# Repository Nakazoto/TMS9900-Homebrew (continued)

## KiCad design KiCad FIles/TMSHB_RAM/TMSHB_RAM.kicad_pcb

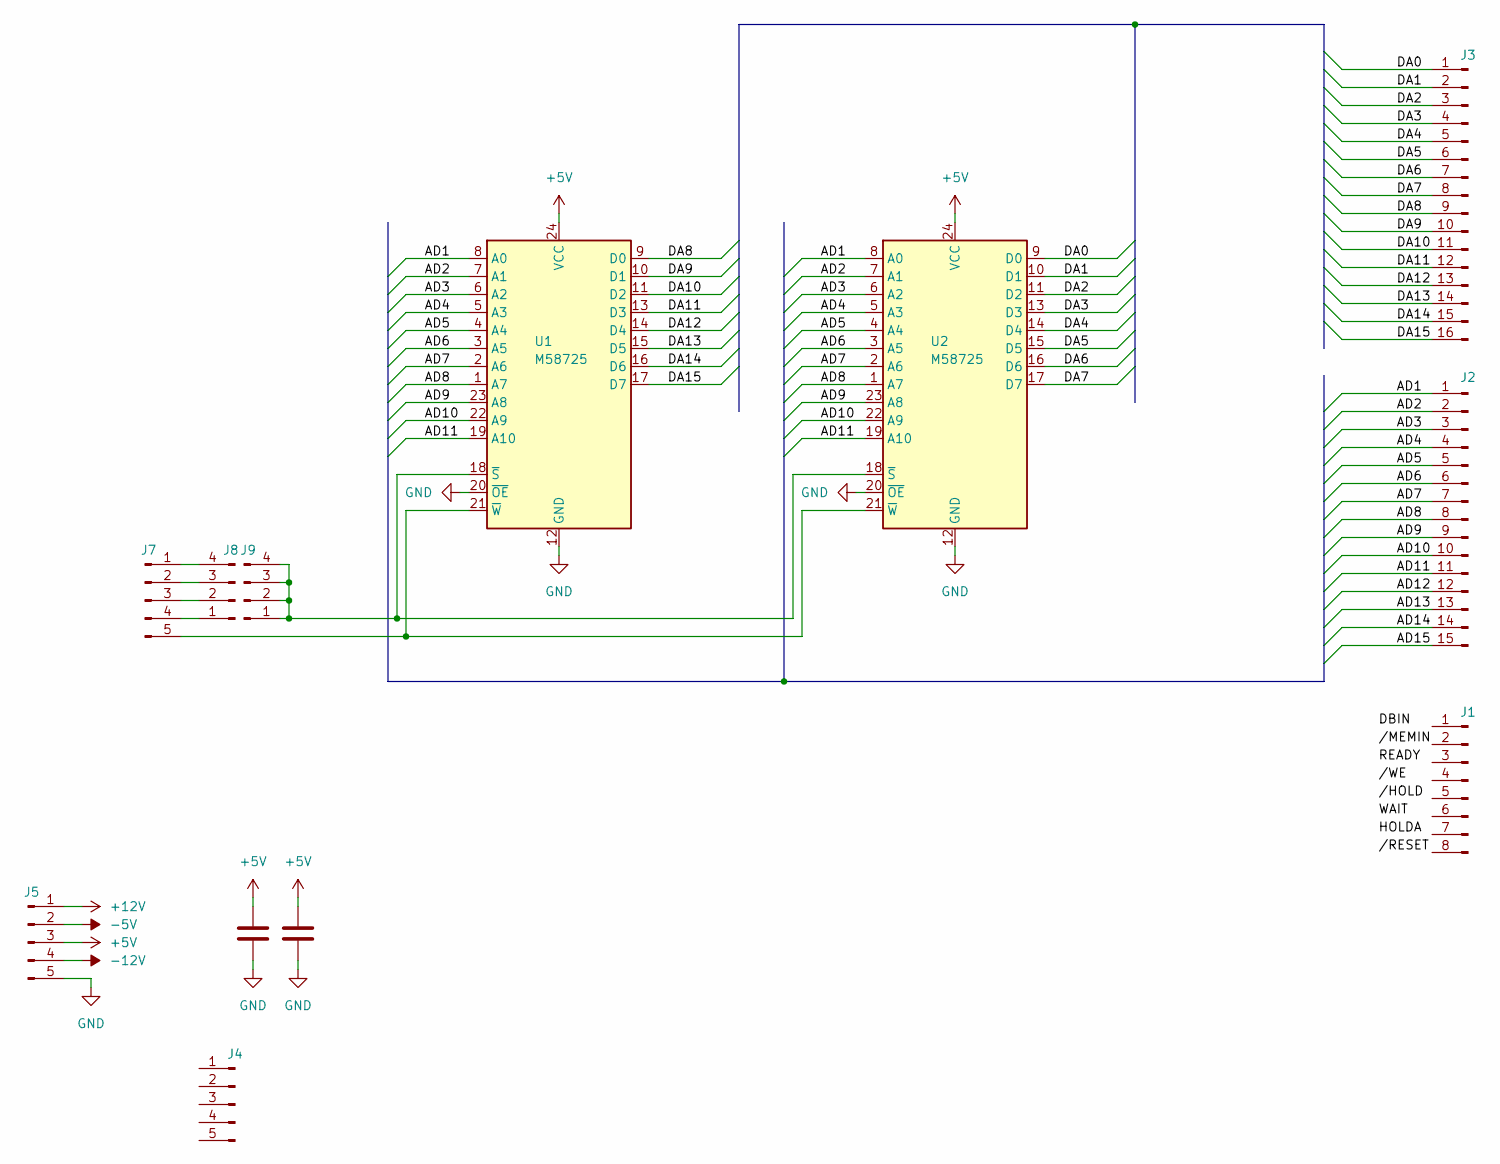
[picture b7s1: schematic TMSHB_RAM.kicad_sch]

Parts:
C1, C2: C; C_Disc_D3.0mm_W1.6mm_P2.50mm
J1: Conn_01x08_Pin; PinHeader_1x08_P2.54mm_Vertical
J2: Conn_01x15_Pin; PinHeader_1x15_P2.54mm_Vertical
J3: Conn_01x16_Pin; PinHeader_1x16_P2.54mm_Vertical
J4, J5, J7: Conn_01x05_Pin; PinHeader_1x05_P2.54mm_Vertical
J8, J9: Conn_01x04_Pin; PinHeader_1x04_P2.54mm_Vertical
U1, U2: M58725; DIP-24_W15.24mm

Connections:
+5V: C1.1, C2.1, J5.3, U1.24 (VCC), U2.24 (VCC)
+12V: J5.1
-5V: J5.2
-12V: J5.4
/AD1: J2.1, U1.8 (A0), U2.8 (A0)
/AD2: J2.2, U1.7 (A1), U2.7 (A1)
/AD3: J2.3, U1.6 (A2), U2.6 (A2)
/AD4: J2.4, U1.5 (A3), U2.5 (A3)
/AD5: J2.5, U1.4 (A4), U2.4 (A4)
/AD6: J2.6, U1.3 (A5), U2.3 (A5)
/AD7: J2.7, U1.2 (A6), U2.2 (A6)
/AD8: J2.8, U1.1 (A7), U2.1 (A7)
/AD9: J2.9, U1.23 (A8), U2.23 (A8)
/AD10: J2.10, U1.22 (A9), U2.22 (A9)
/AD11: J2.11, U1.19 (A10), U2.19 (A10)
/AD12: J2.12
/AD13: J2.13
/AD14: J2.14
/AD15: J2.15
/DA0: J3.1, U2.9 (D0)
/DA1: J3.2, U2.10 (D1)
/DA2: J3.3, U2.11 (D2)
/DA3: J3.4, U2.13 (D3)
/DA4: J3.5, U2.14 (D4)
/DA5: J3.6, U2.15 (D5)
/DA6: J3.7, U2.16 (D6)
/DA7: J3.8, U2.17 (D7)
/DA8: J3.9, U1.9 (D0)
/DA9: J3.10, U1.10 (D1)
/DA10: J3.11, U1.11 (D2)
/DA11: J3.12, U1.13 (D3)
/DA12: J3.13, U1.14 (D4)
/DA13: J3.14, U1.15 (D5)
/DA14: J3.15, U1.16 (D6)
/DA15: J3.16, U1.17 (D7)
GND: C1.2, C2.2, J5.5, U1.12 (GND), U1.20 (~OE), U2.12 (GND), U2.20 (~OE)
unnamed: J7.1, J8.4
unnamed: J7.2, J8.3
unnamed: J7.3, J8.2
unnamed: J7.4, J8.1
unnamed: J7.5, U1.21 (~W), U2.21 (~W)
unnamed: J9.1, J9.2, J9.3, J9.4, U1.18 (~S), U2.18 (~S)

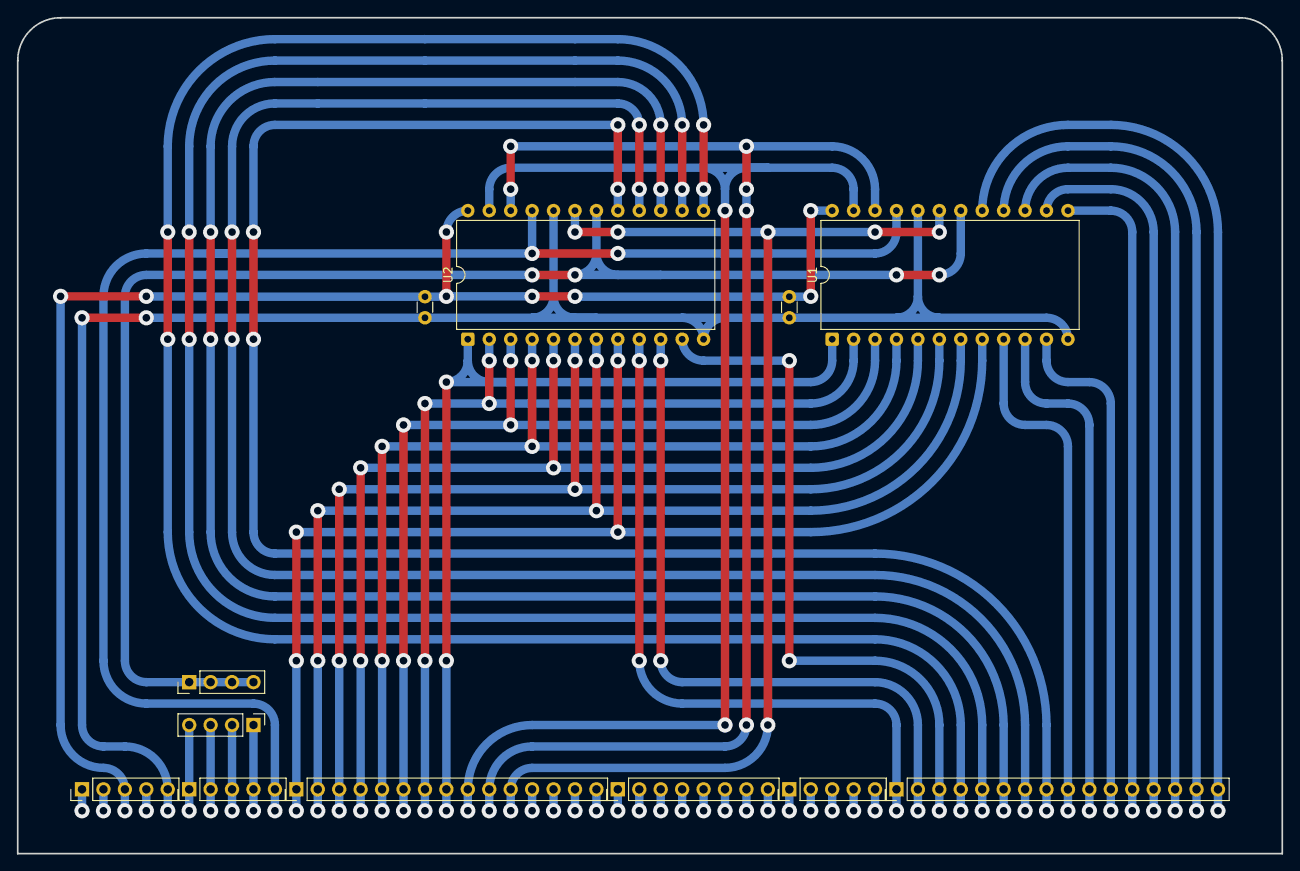
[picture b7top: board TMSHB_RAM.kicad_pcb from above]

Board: 2 copper layers, 149.9 x 99.1 mm, 12 parts (0 on the bottom side), 35 nets.

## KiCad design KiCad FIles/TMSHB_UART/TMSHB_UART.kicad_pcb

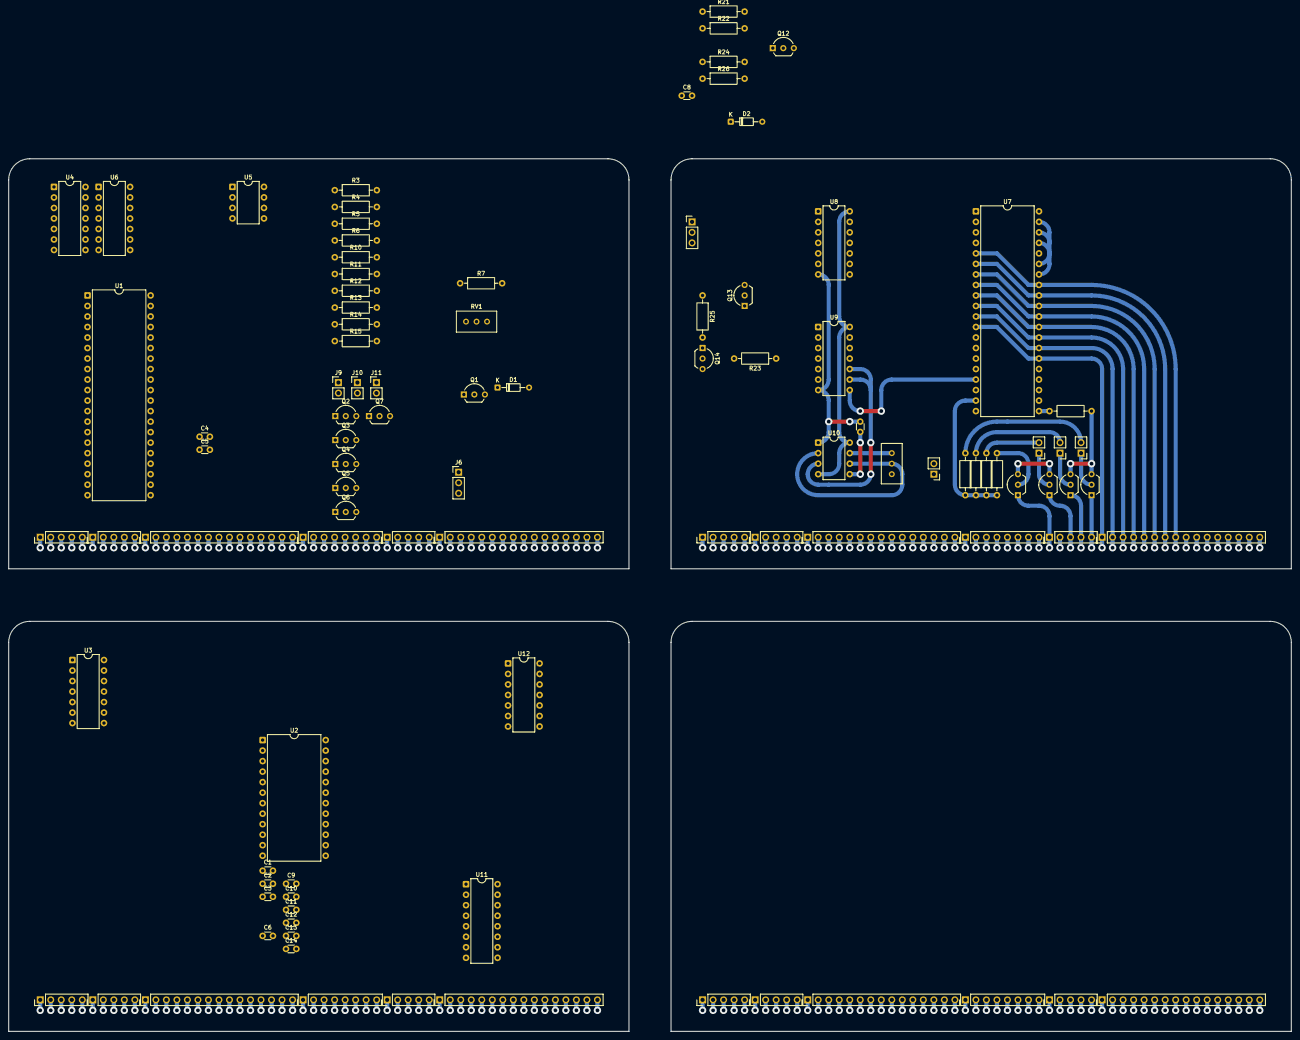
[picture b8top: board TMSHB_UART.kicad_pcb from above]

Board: 2 copper layers, 309.9 x 210.8 mm, 99 parts (0 on the bottom side), 117 nets.

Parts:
C1, C2, C3, C6, C9, C10, C11, C12, C13, C14: C; C_Disc_D3.0mm_W1.6mm_P2.50mm
C4: 470nF; C_Disc_D3.0mm_W1.6mm_P2.50mm
C5, C7: 0.1u; C_Disc_D3.0mm_W1.6mm_P2.50mm
C8: 10nF; C_Disc_D3.0mm_W1.6mm_P2.50mm
D1, D2: D; D_DO-34_SOD68_P7.62mm_Horizontal
J1, J1#2, J1#3, J1#4: Conn_01x08_Pin; PinHeader_1x08_P2.54mm_Vertical
J2, J2#2, J2#3, J2#4: Conn_01x15_Pin; PinHeader_1x15_P2.54mm_Vertical
J3, J3#2, J3#3, J3#4: Conn_01x16_Pin; PinHeader_1x16_P2.54mm_Vertical
J4, J4#2, J4#3, J4#4, J5, J5#2, J5#3, J5#4, J7, J7#2, J7#3, J7#4: Conn_01x05_Pin; PinHeader_1x05_P2.54mm_Vertical
J6, J8: Conn_01x03_Pin; PinHeader_1x03_P2.54mm_Vertical
J9, J10, J11, J12, J13, J14, J14#2: Conn_01x02_Pin; PinHeader_1x02_P2.54mm_Vertical
Q1, Q3, Q4, Q5, Q6, Q7, Q8, Q9, Q10, Q11, Q12, Q13: NPN; TO-92_Inline_Wide
Q2, Q14: PNP; TO-92_Inline_Wide
R3, R11, R16, R22: 4.7k; R_Axial_DIN0207_L6.3mm_D2.5mm_P10.16mm_Horizontal
R4, R26: 1k; R_Axial_DIN0207_L6.3mm_D2.5mm_P10.16mm_Horizontal
R5, R6, R7, R10, R12, R13, R14, R15, R17, R18, R19, R20, R21, R23, R24, R25: 10k; R_Axial_DIN0207_L6.3mm_D2.5mm_P10.16mm_Horizontal
RV1: 5k; Potentiometer_Bourns_3296W_Vertical
RV2: 10k; Potentiometer_Bourns_3296W_Vertical
U1, U7: TR1602; DIP-40_W15.24mm
U2: 27C16; DIP-24_W15.24mm
U3, U6, U8: 74LS00; DIP-14_W7.62mm
U4, U9: 74LS32; DIP-14_W7.62mm
U5, U10: NE555P; DIP-8_W7.62mm
U11: 74LS138; DIP-16_W7.62mm
U12: 74LS04; DIP-14_W7.62mm

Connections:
+5V: C1.1, C2.1, C3.1, C6.1, C9.1, C10.1, C11.1, C12.1, C13.1, C14.1, J5.3, J5#2.3, J5#3.3, J5#4.3, Q2.3 (E), Q14.3 (E), R4.1, R11.1, R22.1, R26.1, U1.1 (+5V), U1.16 (SFD), U1.34 (CRL), U1.35 (PI), U1.37 (WSL2), U1.38 (WSL1), U1.39 (EPE), U2.21 (VPP), U2.24 (VCC), U3.14 (VCC), U4.14 (VCC), U5.4 (R), U5.8 (VCC), U6.14 (VCC), U7.1 (+5V), U7.16 (SFD), U7.34 (CRL), U7.35 (PI), U7.37 (WSL2), U7.38 (WSL1), U7.39 (EPE), U8.14 (VCC), U9.14 (VCC), U10.4 (R), U10.8 (VCC), U11.6 (E3), U11.16 (VCC), U12.14 (VCC)
+12V: J5.1, J5#2.1, J5#3.1, J5#4.1
-5V: J5.2, J5#2.2, J5#3.2, J5#4.2
-12V: J5.4, J5#2.4, J5#3.4, J5#4.4, R7.1, R25.1, U1.2 (-12V), U7.2 (-12V)
/AD1: J2.1, J2#2.1, J2#3.1, J2#4.1, U2.8 (A0)
/AD2: J2.2, J2#2.2, J2#3.2, J2#4.2, U2.7 (A1)
/AD3: J2.3, J2#2.3, J2#3.3, J2#4.3, U2.6 (A2)
/AD4: J2.4, J2#2.4, J2#3.4, J2#4.4, U2.5 (A3)
/AD5: J2.5, J2#2.5, J2#3.5, J2#4.5, U2.4 (A4)
/AD6: J2.6, J2#2.6, J2#3.6, J2#4.6, U2.3 (A5)
/AD7: J2.7, J2#2.7, J2#3.7, J2#4.7, U2.2 (A6)
/AD8: J2.8, J2#2.8, J2#3.8, J2#4.8, U2.1 (A7)
/AD9: J2.9, J2#2.9, J2#3.9, J2#4.9, U2.23 (A8)
/AD10: J2.10, J2#2.10, J2#3.10, J2#4.10, U2.22 (A9)
/AD11: J2.11, J2#2.11, J2#3.11, J2#4.11, U2.19 (A10)
/AD12: J2.12, J2#2.12, J2#3.12, J2#4.12, U3.1
/AD13: J2.13, J2#2.13, J2#3.13, J2#4.13, U3.2
/AD14: J2.14, J2#2.14, J2#3.14, J2#4.14, U3.4
/AD15: J2.15, J2#2.15, J2#3.15, J2#4.15, U3.5
/DA8: J3.9, J3#2.9, J3#3.9, J3#4.9
/DA9: J3.10, J3#2.10, J3#3.10, J3#4.10
/DA10: J3.11, J3#2.11, J3#3.11, J3#4.11
/DA11: J3.12, J3#2.12, J3#3.12, J3#4.12
/DA12: J3.13, J3#2.13, J3#3.13, J3#4.13
/DA13: J3.14, J3#2.14, J3#3.14, J3#4.14
/DA14: J3.15, J3#2.15, J3#3.15, J3#4.15
/DA15: J3.16, J3#2.16, J3#3.16, J3#4.16
/DBIN: J1.1, J1#2.1, J1#3.1, J1#4.1
/HOLDA: J1.7, J1#2.7, J1#3.7, J1#4.7
/READY: J1.3, J1#2.3, J1#3.3, J1#4.3
/WAIT: J1.6, J1#2.6, J1#3.6, J1#4.6
//HOLD: J1.5, J1#2.5, J1#3.5, J1#4.5
//MEMIN: J1.2, J1#2.2, J1#3.2, J1#4.2
//RESET: J1.8, J1#2.8, J1#3.8, J1#4.8
//WE: J1.4, J1#2.4, J1#3.4, J1#4.4
DA0: J3.1, J3#2.1, J3#3.1, J3#4.1, Q1.1 (C), Q12.1 (C), U1.12 (RR1), U1.26 (TR1), U7.12 (RR1), U7.26 (TR1)
DA1: J3.2, J3#2.2, J3#3.2, J3#4.2, U1.11 (RR2), U1.27 (TR2), U7.11 (RR2), U7.27 (TR2)
DA2: J3.3, J3#2.3, J3#3.3, J3#4.3, U1.10 (RR3), U1.28 (TR3), U7.10 (RR3), U7.28 (TR3)
DA3: J3.4, J3#2.4, J3#3.4, J3#4.4, U1.9 (RR4), U1.29 (TR4), U7.9 (RR4), U7.29 (TR4)
DA4: J3.5, J3#2.5, J3#3.5, J3#4.5, U1.8 (RR5), U1.30 (TR5), U7.8 (RR5), U7.30 (TR5)
DA5: J3.6, J3#2.6, J3#3.6, J3#4.6, U1.7 (RR6), U1.31 (TR6), U7.7 (RR6), U7.31 (TR6)
DA6: J3.7, J3#2.7, J3#3.7, J3#4.7, U1.6 (RR7), U1.32 (TR7), U7.6 (RR7), U7.32 (TR7)
DA7: J3.8, J3#2.8, J3#3.8, J3#4.8, U1.5 (RR8), U1.33 (TR8), U7.5 (RR8), U7.33 (TR8)
GND: C1.2, C2.2, C3.2, C4.2, C5.1, C6.2, C7.1, C8.2, C9.2, C10.2, C11.2, C12.2, C13.2, C14.2, D1.2 (A), D2.2 (A), J5.5, J5#2.5, J5#3.5, J5#4.5, J6.3, J8.3, Q1.3 (E), Q3.3 (E), Q4.3 (E), Q5.3 (E), Q6.3 (E), Q7.3 (E), Q8.3 (E), Q9.3 (E), Q10.3 (E), Q11.3 (E), Q12.3 (E), Q13.3 (E), R3.1, R16.1, U1.3 (GND), U1.36 (SBS), U2.12 (GND), U2.18 (~CE), U3.7 (GND), U3.12, U3.13, U4.7 (GND), U4.12, U4.13, U5.1 (GND), U6.7 (GND), U6.9, U6.10, U6.12, U6.13, U7.3 (GND), U7.36 (SBS), U8.7 (GND), U8.9, U8.10, U8.12, U8.13, U9.7 (GND), U9.12, U9.13, U10.1 (GND), U11.8 (GND), U12.7 (GND)
IC0: J4.2, J4#2.2, J4#3.2, J4#4.2
IC1: J4.3, J4#2.3, J4#3.3, J4#4.3, Q5.1 (C), Q9.1 (C)
IC2: J4.4, J4#2.4, J4#3.4, J4#4.4, Q6.1 (C), Q10.1 (C)
IC3: J4.5, J4#2.5, J4#3.5, J4#4.5, Q7.1 (C), Q11.1 (C)
IRQ: J4.1, J4#2.1, J4#3.1, J4#4.1, Q4.1 (C), Q8.1 (C)
unnamed: D1.1 (K), Q3.2 (B), R10.1
unnamed: D2.1 (K), Q13.2 (B), R24.1
unnamed: J6.1, R10.2
unnamed: J6.2, Q2.1 (C), R7.2
unnamed: J8.1, R24.2
unnamed: J8.2, Q14.1 (C), R25.2
unnamed: J9.1, Q7.2 (B)
unnamed: J9.2, R15.2
unnamed: J10.1, Q6.2 (B)
unnamed: J10.2, R14.2
unnamed: J11.1, Q5.2 (B)
unnamed: J11.2, R13.2
unnamed: J12.1, Q9.2 (B)
unnamed: J12.2, R18.2
unnamed: J13.1, Q10.2 (B)
unnamed: J13.2, R19.2
unnamed: J14.1, Q11.2 (B)
unnamed: J14.2, R20.2
unnamed: Q1.2 (B), R5.2
unnamed: Q2.2 (B), R6.2
unnamed: Q3.1 (C), R11.2, U4.1, U4.2
unnamed: Q4.2 (B), R12.2
unnamed: Q8.2 (B), R17.2
unnamed: Q12.2 (B), R21.2
unnamed: Q13.1 (C), R22.2, U9.1, U9.2
unnamed: Q14.2 (B), R23.2
unnamed: R5.1, U6.6
unnamed: R6.1, U4.6
unnamed: R21.1, U8.6
unnamed: R23.1, U9.6
unnamed: R12.1, R13.1, R14.1, R15.1, U1.19 (DR)
unnamed: R3.2, U1.21 (MR)
unnamed: U1.20 (RI), U4.3
unnamed: U1.17 (RRC), U1.40 (TRC), U4.8
unnamed: U1.22 (THRE), U6.1
unnamed: U1.25 (TRO), U4.4, U4.5
unnamed: U3.3, U3.9
unnamed: U3.6, U3.10
unnamed: C5.2, U5.5 (CV)
unnamed: R4.2, RV1.3, U5.7 (DIS)
unnamed: U4.9, U4.10, U5.3 (Q)
unnamed: C4.1, RV1.2, U5.2 (TR), U5.6 (THR)
unnamed: U6.3, U6.4, U6.5
unnamed: R17.1, R18.1, R19.1, R20.1, U7.19 (DR)
unnamed: R16.2, U7.21 (MR)
unnamed: U7.20 (RI), U9.3
unnamed: U7.17 (RRC), U7.40 (TRC), U9.8
unnamed: U7.22 (THRE), U8.1
unnamed: U7.25 (TRO), U9.4, U9.5
unnamed: U8.3, U8.4, U8.5
unnamed: C7.2, U10.5 (CV)
unnamed: R26.2, RV2.3, U10.7 (DIS)
unnamed: U9.9, U9.10, U10.3 (Q)
unnamed: C8.1, RV2.2, U10.2 (TR), U10.6 (THR)
unnamed: U2.9 (D0), U11.1 (A0)
unnamed: U2.10 (D1), U11.2 (A1)
unnamed: U2.11 (D2), U11.3 (A2)
unnamed: U2.20 (~OE), U3.8, U11.4 (E1), U11.5 (E2)
unnamed: U11.15 (O0), U12.1
unnamed: U11.11 (O4), U12.3
RRD1: U1.4 (RRD), U11.12 (O3)
RRD2: U7.4 (RRD), U11.7 (O7)
THRE1: U6.2, U12.2
THRE2: U8.2, U12.4
/DRR1: U1.18 (DRR), U11.13 (O2)
/DRR2: U7.18 (DRR), U11.9 (O6)
/THRL1: U1.23 (THRL), U11.14 (O1)
/THRL2: U7.23 (THRL), U11.10 (O5)

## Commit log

2026-01-13 2026/1/13
2026-01-16 2026/1/15
2026-02-11 2025/2/10
2026-03-05 2026/3/5
2026-04-06 2026/4/6
2026-04-07 2026/4/7
2026-04-09 2026/4/9
2026-06-10 2026/6/10
